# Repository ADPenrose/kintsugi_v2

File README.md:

# Kintsugi V2
Repository for the Kintsugi v2 keyboard.

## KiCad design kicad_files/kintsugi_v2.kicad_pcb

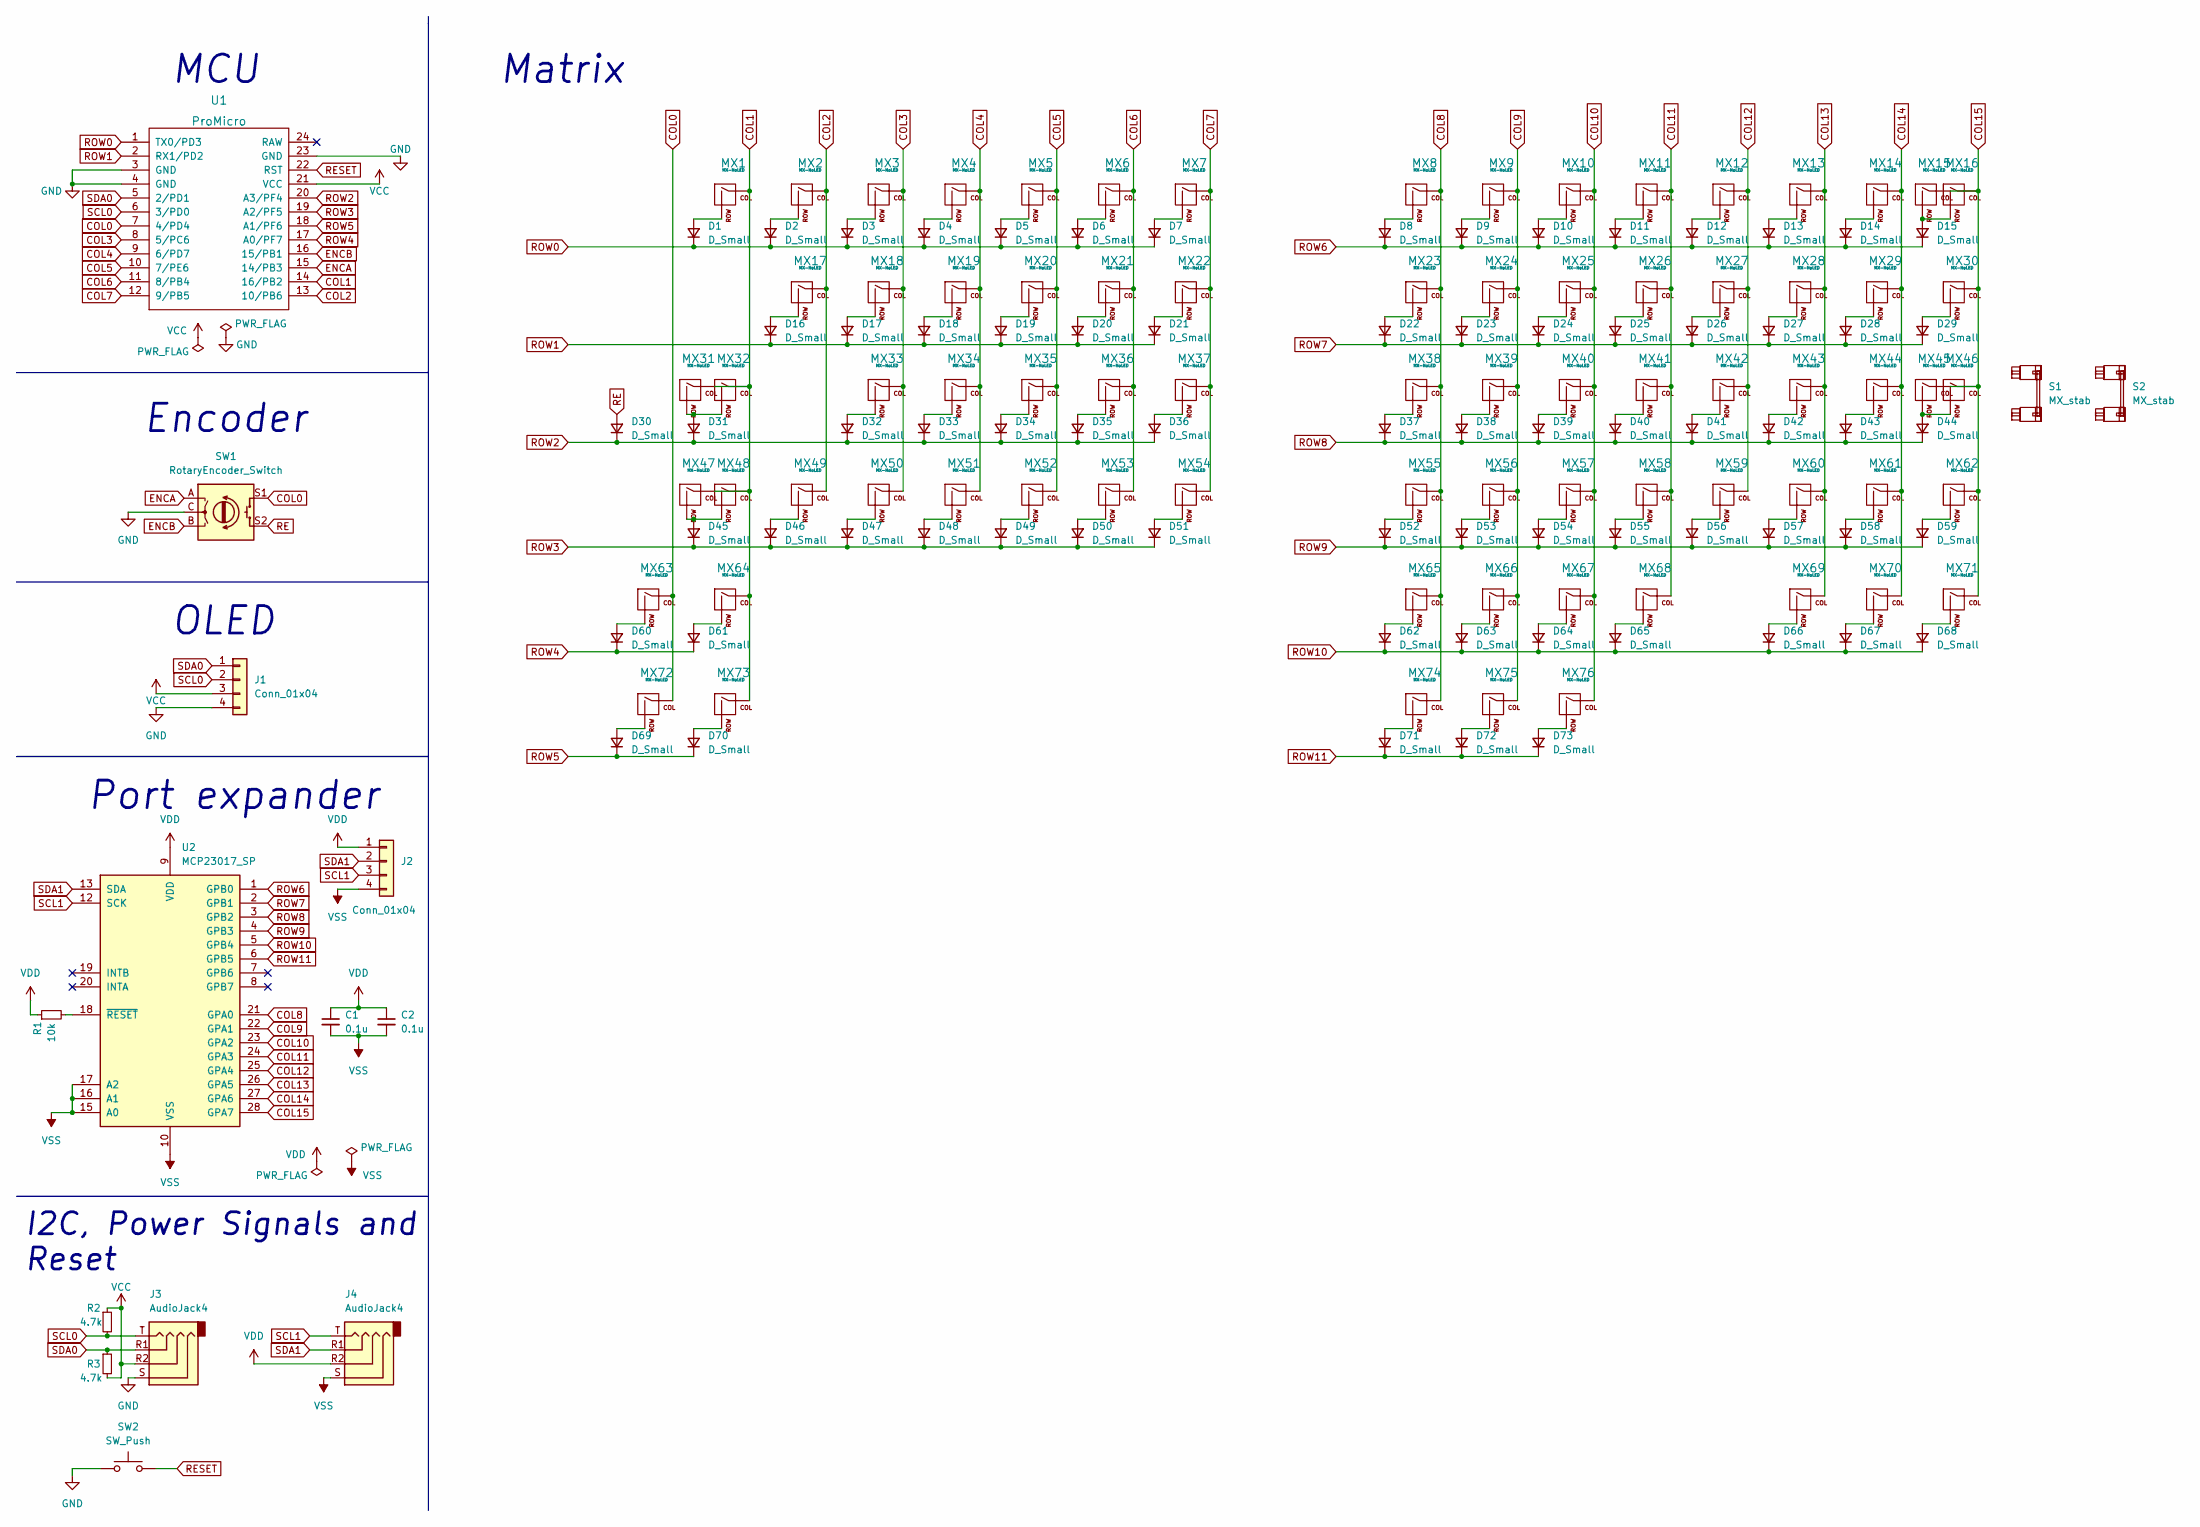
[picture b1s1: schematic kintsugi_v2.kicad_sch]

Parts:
C1, C2: 0.1u; C_0805_2012Metric_Pad1.18x1.45mm_HandSolder
D1, D2, D3, D4, D5, D6, D7, D8, D9, D10, D11, D12, D13, D14, D15, D16, D17, D18, D19, D20, D21, D22, D23, D24, D25, D26, D27, D28, D29, D30, D31, D32, D33, D34, D35, D36, D37, D38, D39, D40, D41, D42, D43, D44, D45, D46, D47, D48, D49, D50, D51, D52, D53, D54, D55, D56, D57, D58, D59, D60, D61, D62, D63, D64, D65, D66, D67, D68, D69, D70, D71, D72, D73: D_Small; D_SOD-123_silkscreen
J1, J2: Conn_01x04; PinHeader_1x04_P2.54mm_Vertical
J3, J4: AudioJack4; TRRS-PJ-320A
MX1, MX2, MX3, MX4, MX5, MX6, MX7, MX8, MX9, MX10, MX11, MX12, MX13, MX14, MX15, MX18, MX19, MX20, MX21, MX22, MX23, MX24, MX25, MX26, MX27, MX28, MX29, MX30, MX33, MX34, MX35, MX36, MX37, MX38, MX39, MX40, MX41, MX42, MX43, MX44, MX45, MX46, MX49, MX50, MX51, MX52, MX53, MX54, MX55, MX56, MX57, MX58, MX59, MX61, MX62, MX69, MX70, MX71, MX74, MX75, MX76: MX-NoLED; MX100H
MX16: MX-NoLED; MX200H
MX17: MX-NoLED; MX150H
MX31, MX47, MX63, MX64, MX66, MX67, MX68, MX72: MX-NoLED; MX125H
MX32, MX60: MX-NoLED; MX175H
MX48: MX-NoLED; MX225H
MX65: MX-NoLED; MX225HR
MX73: MX-NoLED; MX275HR
R1: 10k; R_0805_2012Metric_Pad1.20x1.40mm_HandSolder
R2, R3: 4.7k; R_0805_2012Metric_Pad1.20x1.40mm_HandSolder
S1: MX_stab; STAB_MX_ISO_FLIPPED
S2: MX_stab; STAB_MX_2.25u
SW1: RotaryEncoder_Switch; RotaryEncoder_Alps_EC11E-Switch_Vertical_H20mm
SW2: SW_Push; SW_SPST_SKQG_WithStem
U1: ProMicro; ArduinoProMicro
U2: MCP23017_SP; DIP-28_W7.62mm

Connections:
COL0: MX63.1 (COL), MX72.1 (COL), SW1.S1, U1.7 (4/PD4)
COL1: MX1.1 (COL), MX31.1 (COL), MX32.1 (COL), MX47.1 (COL), MX48.1 (COL), MX64.1 (COL), MX73.1 (COL), U1.14 (16/PB2)
COL2: MX2.1 (COL), MX17.1 (COL), MX49.1 (COL), U1.13 (10/PB6)
COL3: MX3.1 (COL), MX18.1 (COL), MX33.1 (COL), MX50.1 (COL), U1.8 (5/PC6)
COL4: MX4.1 (COL), MX19.1 (COL), MX34.1 (COL), MX51.1 (COL), U1.9 (6/PD7)
COL5: MX5.1 (COL), MX20.1 (COL), MX35.1 (COL), MX52.1 (COL), U1.10 (7/PE6)
COL6: MX6.1 (COL), MX21.1 (COL), MX36.1 (COL), MX53.1 (COL), U1.11 (8/PB4)
COL7: MX7.1 (COL), MX22.1 (COL), MX37.1 (COL), MX54.1 (COL), U1.12 (9/PB5)
COL8: MX8.1 (COL), MX23.1 (COL), MX38.1 (COL), MX55.1 (COL), MX65.1 (COL), MX74.1 (COL), U2.21 (GPA0)
COL9: MX9.1 (COL), MX24.1 (COL), MX39.1 (COL), MX56.1 (COL), MX66.1 (COL), MX75.1 (COL), U2.22 (GPA1)
COL10: MX10.1 (COL), MX25.1 (COL), MX40.1 (COL), MX57.1 (COL), MX67.1 (COL), MX76.1 (COL), U2.23 (GPA2)
COL11: MX11.1 (COL), MX26.1 (COL), MX41.1 (COL), MX58.1 (COL), MX68.1 (COL), U2.24 (GPA3)
COL12: MX12.1 (COL), MX27.1 (COL), MX42.1 (COL), MX59.1 (COL), U2.25 (GPA4)
COL13: MX13.1 (COL), MX28.1 (COL), MX43.1 (COL), MX60.1 (COL), MX69.1 (COL), U2.26 (GPA5)
COL14: MX14.1 (COL), MX29.1 (COL), MX44.1 (COL), MX61.1 (COL), MX70.1 (COL), U2.27 (GPA6)
COL15: MX15.1 (COL), MX16.1 (COL), MX30.1 (COL), MX45.1 (COL), MX46.1 (COL), MX62.1 (COL), MX71.1 (COL), U2.28 (GPA7)
ENCA: SW1.A, U1.15 (14/PB3)
ENCB: SW1.B, U1.16 (15/PB1)
GND: J1.4, J3.S, SW1.C, SW2.1, U1.3 (GND), U1.4 (GND), U1.23 (GND)
unnamed: D1.2 (A), MX1.2 (ROW)
unnamed: D2.2 (A), MX2.2 (ROW)
unnamed: D3.2 (A), MX3.2 (ROW)
unnamed: D4.2 (A), MX4.2 (ROW)
unnamed: D5.2 (A), MX5.2 (ROW)
unnamed: D6.2 (A), MX6.2 (ROW)
unnamed: D7.2 (A), MX7.2 (ROW)
unnamed: D8.2 (A), MX8.2 (ROW)
unnamed: D9.2 (A), MX9.2 (ROW)
unnamed: D10.2 (A), MX10.2 (ROW)
unnamed: D11.2 (A), MX11.2 (ROW)
unnamed: D12.2 (A), MX12.2 (ROW)
unnamed: D13.2 (A), MX13.2 (ROW)
unnamed: D14.2 (A), MX14.2 (ROW)
unnamed: D15.2 (A), MX15.2 (ROW), MX16.2 (ROW)
unnamed: D16.2 (A), MX17.2 (ROW)
unnamed: D17.2 (A), MX18.2 (ROW)
unnamed: D18.2 (A), MX19.2 (ROW)
unnamed: D19.2 (A), MX20.2 (ROW)
unnamed: D20.2 (A), MX21.2 (ROW)
unnamed: D21.2 (A), MX22.2 (ROW)
unnamed: D22.2 (A), MX23.2 (ROW)
unnamed: D23.2 (A), MX24.2 (ROW)
unnamed: D24.2 (A), MX25.2 (ROW)
unnamed: D25.2 (A), MX26.2 (ROW)
unnamed: D26.2 (A), MX27.2 (ROW)
unnamed: D27.2 (A), MX28.2 (ROW)
unnamed: D28.2 (A), MX29.2 (ROW)
unnamed: D29.2 (A), MX30.2 (ROW)
unnamed: D31.2 (A), MX31.2 (ROW), MX32.2 (ROW)
unnamed: D32.2 (A), MX33.2 (ROW)
unnamed: D33.2 (A), MX34.2 (ROW)
unnamed: D34.2 (A), MX35.2 (ROW)
unnamed: D35.2 (A), MX36.2 (ROW)
unnamed: D36.2 (A), MX37.2 (ROW)
unnamed: D37.2 (A), MX38.2 (ROW)
unnamed: D38.2 (A), MX39.2 (ROW)
unnamed: D39.2 (A), MX40.2 (ROW)
unnamed: D40.2 (A), MX41.2 (ROW)
unnamed: D41.2 (A), MX42.2 (ROW)
unnamed: D42.2 (A), MX43.2 (ROW)
unnamed: D43.2 (A), MX44.2 (ROW)
unnamed: D44.2 (A), MX45.2 (ROW), MX46.2 (ROW)
unnamed: D45.2 (A), MX47.2 (ROW), MX48.2 (ROW)
unnamed: D46.2 (A), MX49.2 (ROW)
unnamed: D47.2 (A), MX50.2 (ROW)
unnamed: D48.2 (A), MX51.2 (ROW)
unnamed: D49.2 (A), MX52.2 (ROW)
unnamed: D50.2 (A), MX53.2 (ROW)
unnamed: D51.2 (A), MX54.2 (ROW)
unnamed: D52.2 (A), MX55.2 (ROW)
unnamed: D53.2 (A), MX56.2 (ROW)
unnamed: D54.2 (A), MX57.2 (ROW)
unnamed: D55.2 (A), MX58.2 (ROW)
unnamed: D56.2 (A), MX59.2 (ROW)
unnamed: D57.2 (A), MX60.2 (ROW)
unnamed: D58.2 (A), MX61.2 (ROW)
unnamed: D59.2 (A), MX62.2 (ROW)
unnamed: D60.2 (A), MX63.2 (ROW)
unnamed: D61.2 (A), MX64.2 (ROW)
unnamed: D62.2 (A), MX65.2 (ROW)
unnamed: D63.2 (A), MX66.2 (ROW)
unnamed: D64.2 (A), MX67.2 (ROW)
unnamed: D65.2 (A), MX68.2 (ROW)
unnamed: D66.2 (A), MX69.2 (ROW)
unnamed: D67.2 (A), MX70.2 (ROW)
unnamed: D68.2 (A), MX71.2 (ROW)
unnamed: D69.2 (A), MX72.2 (ROW)
unnamed: D70.2 (A), MX73.2 (ROW)
unnamed: D71.2 (A), MX74.2 (ROW)
unnamed: D72.2 (A), MX75.2 (ROW)
unnamed: D73.2 (A), MX76.2 (ROW)
unnamed: R1.2, U2.18 (~RESET)
RE: D30.2 (A), SW1.S2
RESET: SW2.2, U1.22 (RST)
ROW0: D1.1 (K), D2.1 (K), D3.1 (K), D4.1 (K), D5.1 (K), D6.1 (K), D7.1 (K), U1.1 (TX0/PD3)
ROW1: D16.1 (K), D17.1 (K), D18.1 (K), D19.1 (K), D20.1 (K), D21.1 (K), U1.2 (RX1/PD2)
ROW2: D30.1 (K), D31.1 (K), D32.1 (K), D33.1 (K), D34.1 (K), D35.1 (K), D36.1 (K), U1.20 (A3/PF4)
ROW3: D45.1 (K), D46.1 (K), D47.1 (K), D48.1 (K), D49.1 (K), D50.1 (K), D51.1 (K), U1.19 (A2/PF5)
ROW4: D60.1 (K), D61.1 (K), U1.17 (A0/PF7)
ROW5: D69.1 (K), D70.1 (K), U1.18 (A1/PF6)
ROW6: D8.1 (K), D9.1 (K), D10.1 (K), D11.1 (K), D12.1 (K), D13.1 (K), D14.1 (K), D15.1 (K), U2.1 (GPB0)
ROW7: D22.1 (K), D23.1 (K), D24.1 (K), D25.1 (K), D26.1 (K), D27.1 (K), D28.1 (K), D29.1 (K), U2.2 (GPB1)
ROW8: D37.1 (K), D38.1 (K), D39.1 (K), D40.1 (K), D41.1 (K), D42.1 (K), D43.1 (K), D44.1 (K), U2.3 (GPB2)
ROW9: D52.1 (K), D53.1 (K), D54.1 (K), D55.1 (K), D56.1 (K), D57.1 (K), D58.1 (K), D59.1 (K), U2.4 (GPB3)
ROW10: D62.1 (K), D63.1 (K), D64.1 (K), D65.1 (K), D66.1 (K), D67.1 (K), D68.1 (K), U2.5 (GPB4)
ROW11: D71.1 (K), D72.1 (K), D73.1 (K), U2.6 (GPB5)
SCL0: J1.2, J3.T, R2.2, U1.6 (3/PD0)
SCL1: J2.3, J4.T, U2.12 (SCK)
SDA0: J1.1, J3.R1, R3.1, U1.5 (2/PD1)
SDA1: J2.2, J4.R1, U2.13 (SDA)
VCC: J1.3, J3.R2, R2.1, R3.2, U1.21 (VCC)
VDD: C1.1, C2.1, J2.1, J4.R2, R1.1, U2.9 (VDD)
VSS: C1.2, C2.2, J2.4, J4.S, U2.10 (VSS), U2.15 (A0), U2.16 (A1), U2.17 (A2)

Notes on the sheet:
Port expander
MCU
Matrix
OLED
Encoder
I2C, Power Signals and Reset

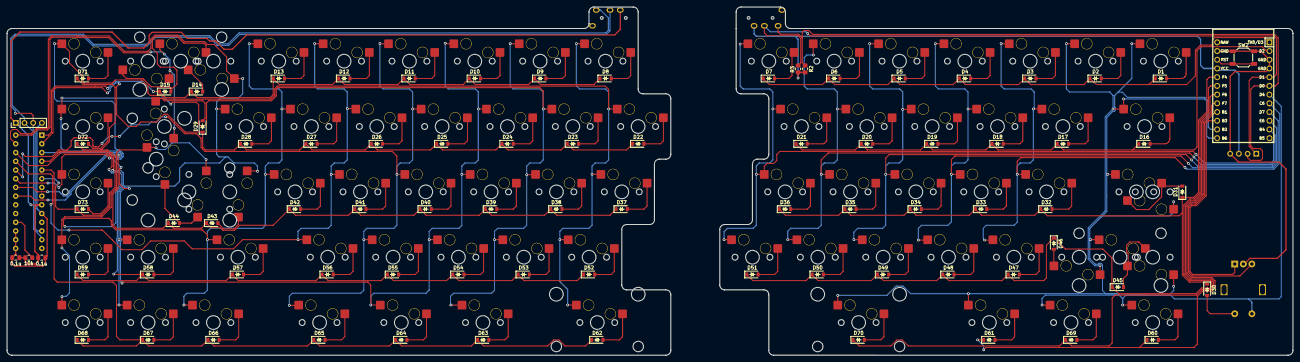
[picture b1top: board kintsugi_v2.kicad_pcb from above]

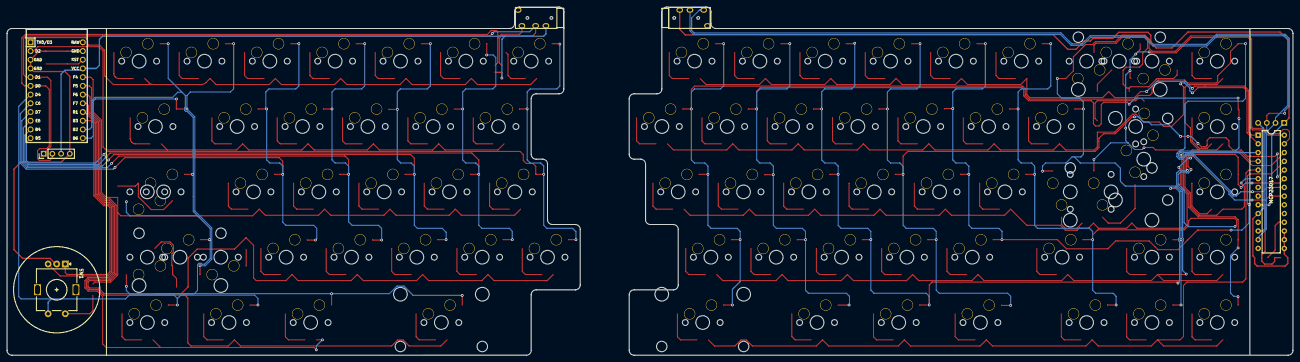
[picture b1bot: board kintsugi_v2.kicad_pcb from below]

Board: 2 copper layers, 374.9 x 101.5 mm, 164 parts (8 on the bottom side), 113 nets.

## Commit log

2022-08-22 Added project files.
2022-08-22 Added LICENSE
2022-08-24 Added first half of schematics.
2022-08-29 Added tentative switch matrix.
2022-09-23 Completed schematic and linked footprints.
2022-09-24 Added preliminary arrangement of the components on the PCB file.
2022-09-25 Fixed an outline.
2022-09-26 Rearranged some components.
2022-09-26 Routed sockets pads to diodes. Pending review.
2022-09-27 Routed rows of the switch matrix.
2022-09-28 Routed cols of the right side (down view) of the keyboard.
2022-09-28 Routed rows of the right side (down view) to the MCU.
2022-09-28 Filleted edge cuts.
2022-09-28 Routed rows of the left side (down view) of the keyboard.
2022-09-28 Re-arranged some traces.
2022-09-29 Finished routing on both sides. DRC and fillets pending.
2022-09-30 Added mousebites, re-arranged PCB and ground-filled half of the keyboard.
2022-09-30 Completed ground fill. Graphics pending.
2022-10-01 Added logos and decorations. Extra part and DRC pending.
2022-10-05 DRC check passed. Pending JLCPCB compatibility confirmation.
2022-10-05 Filleted left side (down view) traces. Right side pending.
2022-10-27 Filleted MCP-side front layer traces.
2022-10-28 Fixed some errors on the layout of the switch matrix.
2022-11-04 Added decorations and DRC'ed the PCB.
2022-11-05 Added mounting holes. Pending DRC.
2022-11-06 Fixed logos and text.
2022-11-07 Added production files.
2022-11-07 Added final production files.
2023-01-06 Added initial case files.
2023-01-07 Added upper case files.
2023-01-08 Added bottom case files.
2023-01-10 Added final case files.
